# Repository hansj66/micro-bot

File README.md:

# Micro:bit sumo robot
Firmware and hardware design files for the [TimeExpander.com](https://www.timeexpander.com/) Micro:bit based robot

The bot features two motor bridges, 3 x time of flight sensors, 4 x reflective object sensors and a GPIO Expander. 

Toolchain for building the firmware is the mBed online compiler.

You can watch one of the demo state machines in action here: https://youtu.be/_6B225iNg58

# V3
There is an untested v3 in the Hardware folder. [See v3 Readme](https://github.com/rosmo-robot/micro-bot/tree/master/Hardware/V3#readme)

# V2

This is the latest tested version.

# v2 Bill of materials
* 1 x Main PCB (https://github.com/hansj66/micro-bot/blob/master/Hardware/minisumo_v2.brd)
* 4 x line sensor PCBs (https://github.com/hansj66/micro-bot/blob/master/Hardware/minisumo_sensor.brd)
* 2 x Wheels (AliExpress)
* 2 x N20 motors (AliExpress)
* 2 x N20 motor bracket assembly (AliExpress)
* 3 x VL53L0X time of flight sensors on a carrier PCB (AliExpress)
* 1 x TCA9539 IO expander (Digikey)
* 1 x TXB0106PWR Bi-directional level translator  (Digikey)
* 4 x QRE1113GR Reflective optical sensors  (Digikey)
* 1 x 100uF aluminium capacitor
* 1 x 2x5 pin 2.54mm female header (Digikey)
* 1 x battery pack for 4x AAA  (Digikey)
* 1 x JS202011SCQN slide switch  (Digikey)
* 1 x SOT223 LM1117 3.3V regulator (Digikey)
* 1 x Mini caster assembly (AliExpress + 3D printed bracket)
* 2 x 3D printed spacers (between motors and PCB)
* 1 x 12 pin male breakaway header  (Digikey)
* 3 x 6 pin RA breakaway header  (Digikey)
* 1 x hook and loop tape (for attaching battery pack)
* 2 x 100nf capacitors (motor noise suppression)

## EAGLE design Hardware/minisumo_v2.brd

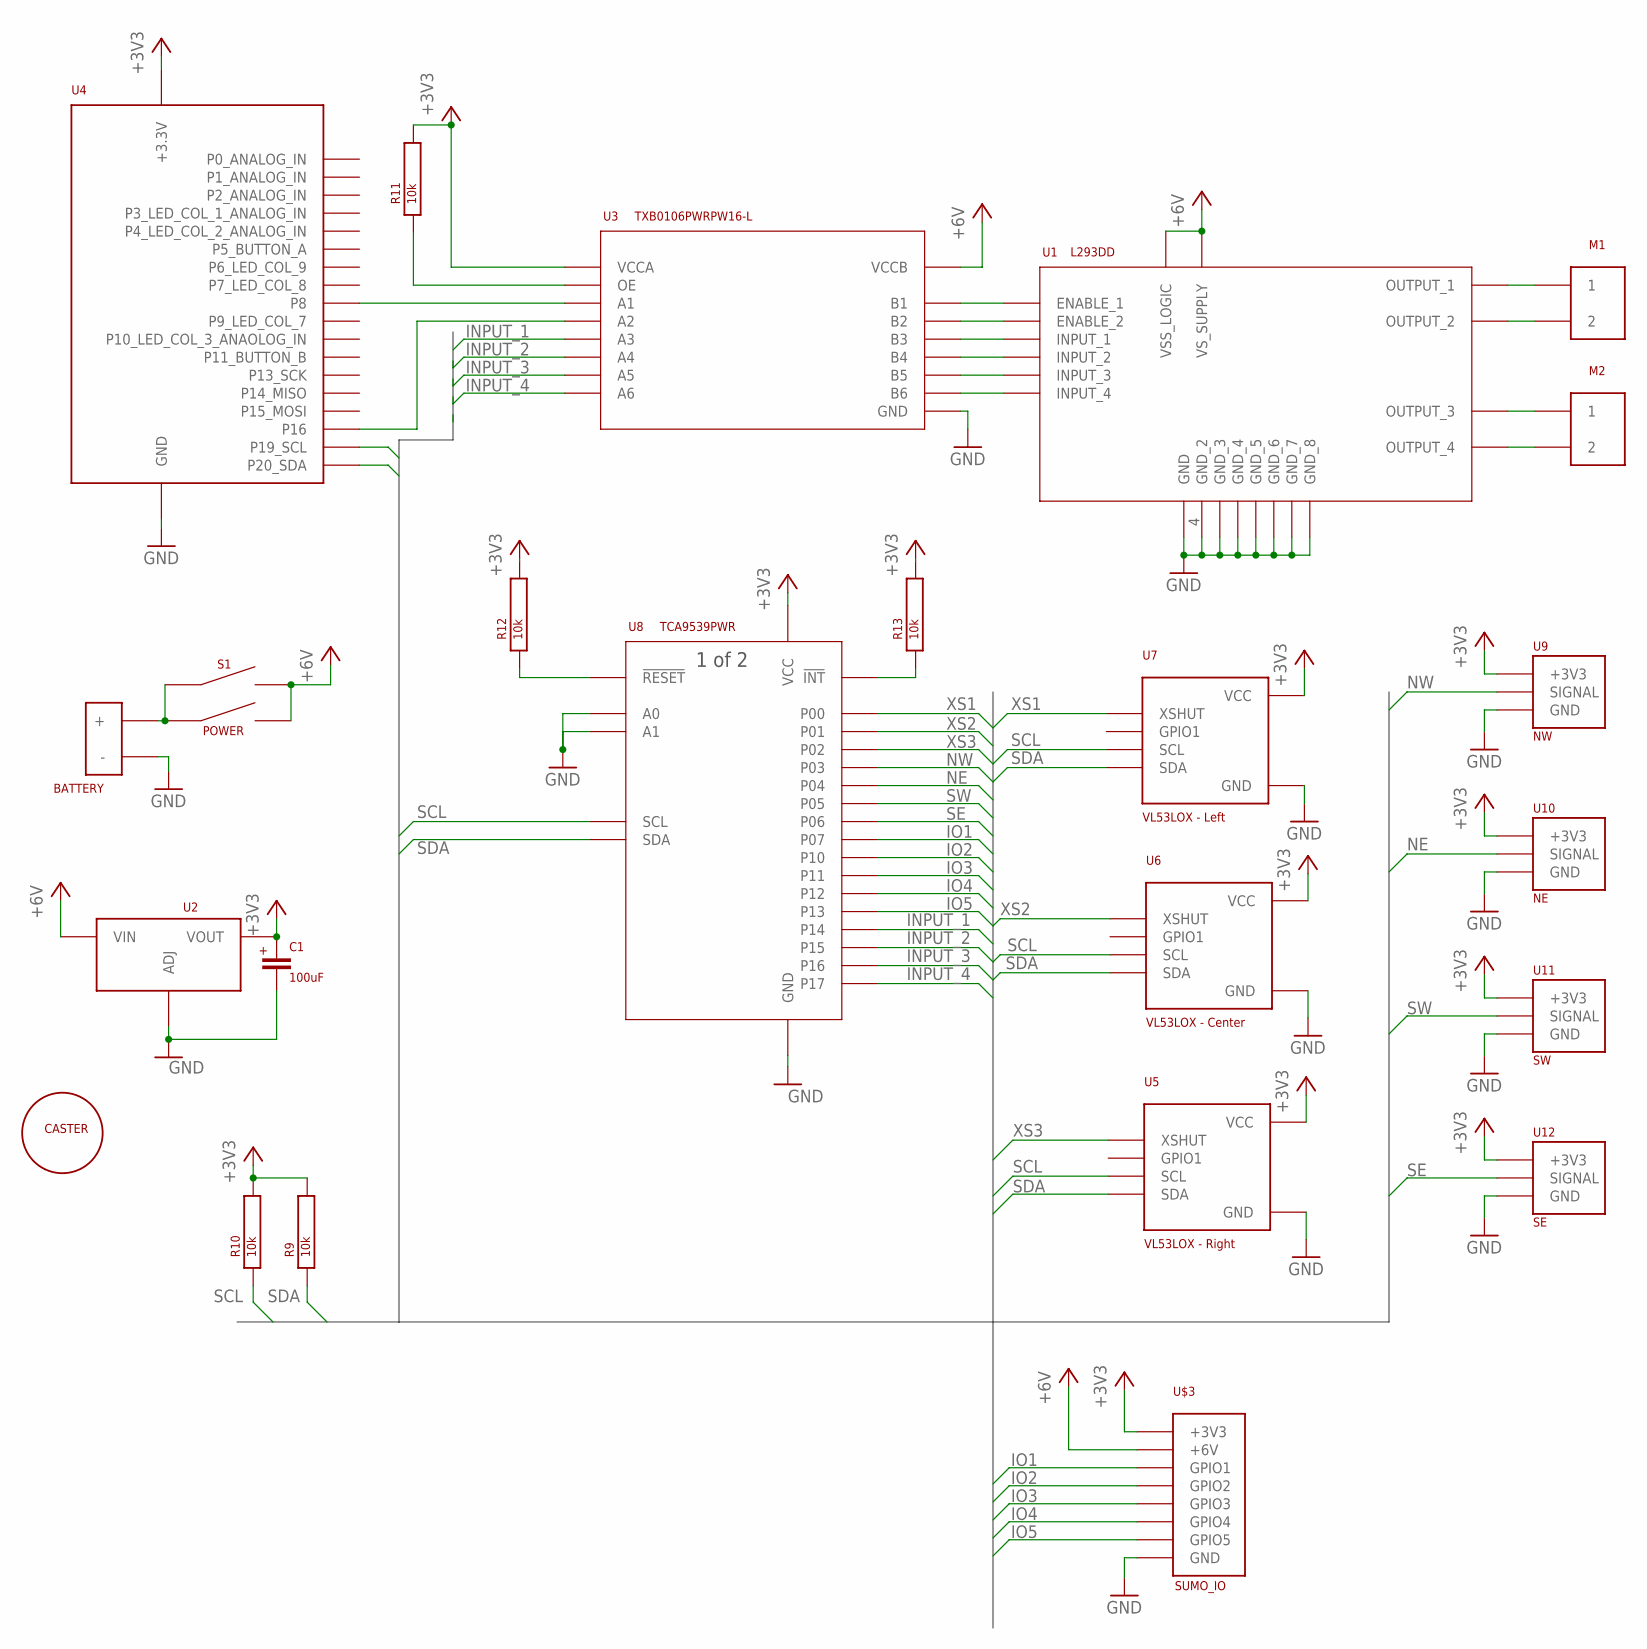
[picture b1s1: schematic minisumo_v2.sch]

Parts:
BATTERY: BATTERY_HOLDER_AAA_2X2
C1: 100uF; ALUMINUM_WURTH_100UF_865080243007
M1, M2: N20_MOTOR; N20-MOTOR-BRACKET
R9, R10, R11, R12, R13: 10k; RES_0402
S1: POWER; SWITCH_JS202011SCQN
U1: L293DD; SO-20
U2: LM1117; SOT-223
U3: TXB0106PWRPW16-L; PW16-L
U4: BBC Micro:bit; CYCLONE_MICROBIT_VERTICAL
U5: VL53LOX - Right; VL53LOX
U6: VL53LOX - Center; VL53LOX
U7: VL53LOX - Left; VL53LOX
U8: TCA9539PWR; 24-TSSOP
U9: NW; QRE1113_MODULE
U10: NE; QRE1113_MODULE
U11: SW; QRE1113_MODULE
U12: SE; QRE1113_MODULE
U$1: CASTER
U$3: SUMO_IO

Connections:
+3V3: C1.+, R9.P$2, R10.P$2, R11.P$2, R12.P$2, R13.P$2, U2.P$2 (VOUT), U2.VOUT$1 (VOUT), U3.2 (VCCA), U4.3.3V@9 (+3.3V), U4.3.3V@10 (+3.3V), U4.3.3V@11 (+3.3V), U4.3.3V@12 (+3.3V), U4.3.3V@13 (+3.3V), U4.3.3V@14 (+3.3V), U5.VCC, U6.VCC, U7.VCC, U8.24 (VCC), U9.+3V3, U10.+3V3, U11.+3V3, U12.+3V3, U$3.3V3 (+3V3)
+5V: S1.3 (B2), S1.6 (B1), U1.10 (VS_SUPPLY), U1.20 (VSS_LOGIC), U2.VIN, U3.15 (VCCB), U$3.6V (+6V)
GND: BATTERY.-, C1.-, U1.4 (GND_2), U1.5 (GND_3), U1.6 (GND_4), U1.7 (GND_5), U1.14 (GND_6), U1.15 (GND_7), U1.16 (GND_8), U1.17 (GND), U2.GND (ADJ), U3.9 (GND), U4.GND@1 (GND), U4.GND@2 (GND), U4.GND@3 (GND), U4.GND@4 (GND), U4.GND@5 (GND), U4.GND@6 (GND), U5.GND, U6.GND, U7.GND, U8.2 (A1), U8.12 (GND), U8.21 (A0), U9.GND, U10.GND, U11.GND, U12.GND, U$3.GND
INPUT_1: U3.4 (A3), U8.17 (P14)
INPUT_2: U3.5 (A4), U8.18 (P15)
INPUT_3: U3.6 (A5), U8.19 (P16)
INPUT_4: U3.7 (A6), U8.20 (P17)
IO1: U8.11 (P07), U$3.GPIO1
IO2: U8.13 (P10), U$3.GPIO2
IO3: U8.14 (P11), U$3.GPIO3
IO4: U8.15 (P12), U$3.GPIO4
IO5: U8.16 (P13), U$3.GPIO5
unnamed: U1.1 (ENABLE_1), U3.16 (B1)
unnamed: U1.11 (ENABLE_2), U3.14 (B2)
unnamed: U1.2 (INPUT_1), U3.13 (B3)
unnamed: U1.9 (INPUT_2), U3.12 (B4)
unnamed: M1.1, U1.3 (OUTPUT_1)
unnamed: M1.2, U1.8 (OUTPUT_2)
unnamed: M2.1, U1.13 (OUTPUT_3)
unnamed: M2.2, U1.18 (OUTPUT_4)
unnamed: U3.1 (A1), U4.P8
unnamed: U1.12 (INPUT_3), U3.11 (B5)
unnamed: U3.3 (A2), U4.P16
unnamed: U1.19 (INPUT_4), U3.10 (B6)
unnamed: BATTERY.+, S1.2 (A2), S1.5 (A1)
unnamed: R11.P$1, U3.8 (OE)
unnamed: R12.P$1, U8.3 (!RESET)
unnamed: R13.P$1, U8.1 (!INT)
NE: U8.8 (P04), U10.SIGNAL
NW: U8.7 (P03), U9.SIGNAL
SCL: R10.P$1, U4.P21_SCL (P19_SCL), U5.SCL, U6.SCL, U7.SCL, U8.22 (SCL)
SDA: R9.P$1, U4.P20_SDA, U5.SDA, U6.SDA, U7.SDA, U8.23 (SDA)
SE: U8.10 (P06), U12.SIGNAL
SW: U8.9 (P05), U11.SIGNAL
XS1: U7.XSHUT, U8.4 (P00)
XS2: U6.XSHUT, U8.5 (P01)
XS3: U5.XSHUT, U8.6 (P02)

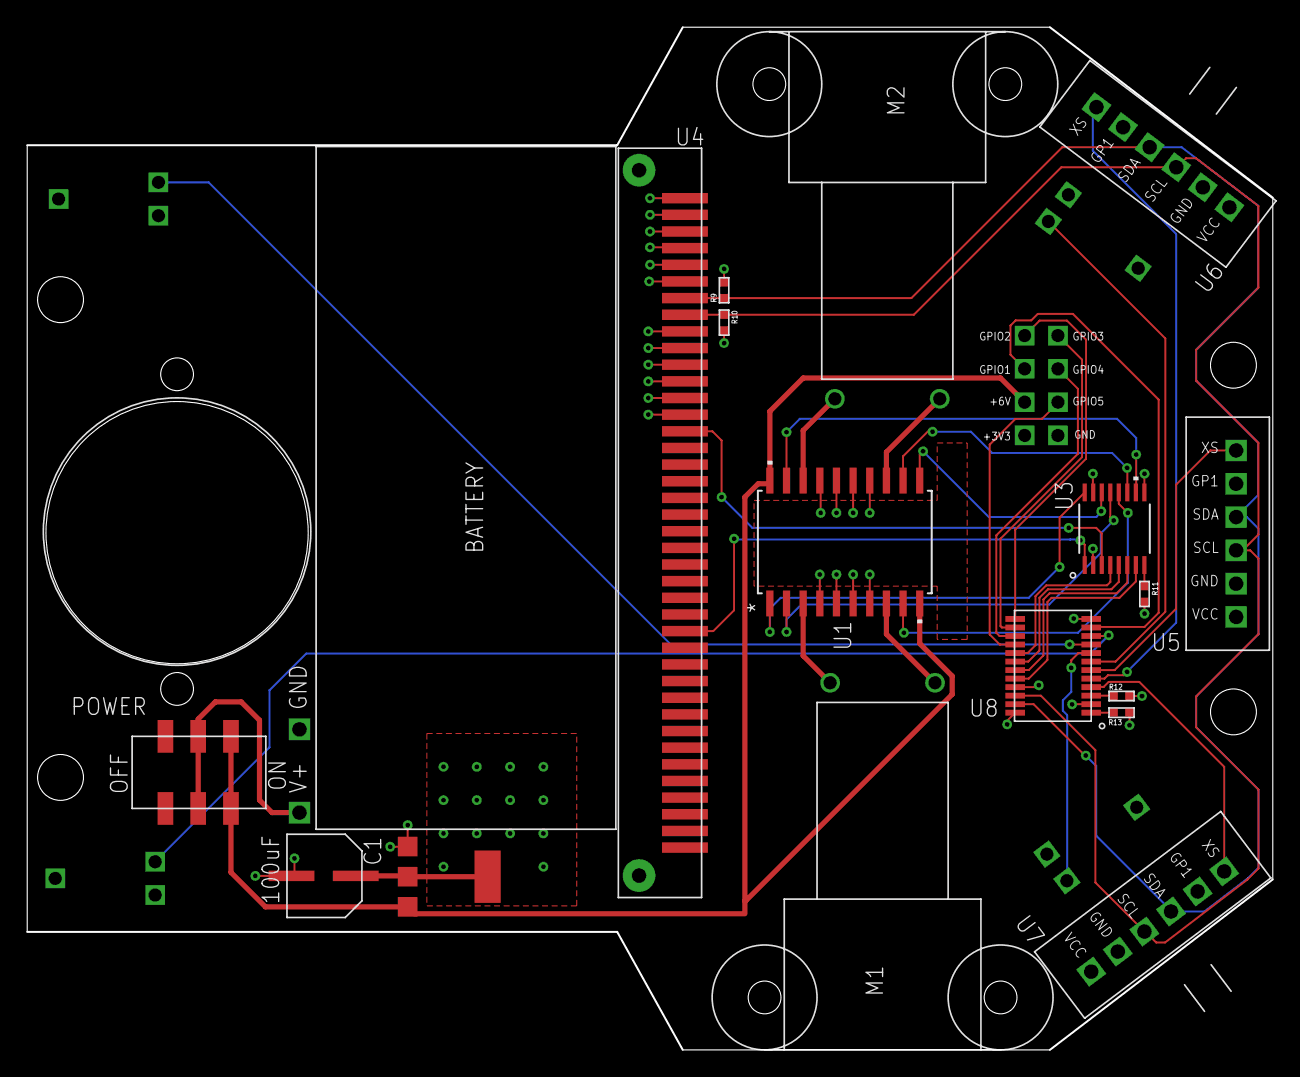
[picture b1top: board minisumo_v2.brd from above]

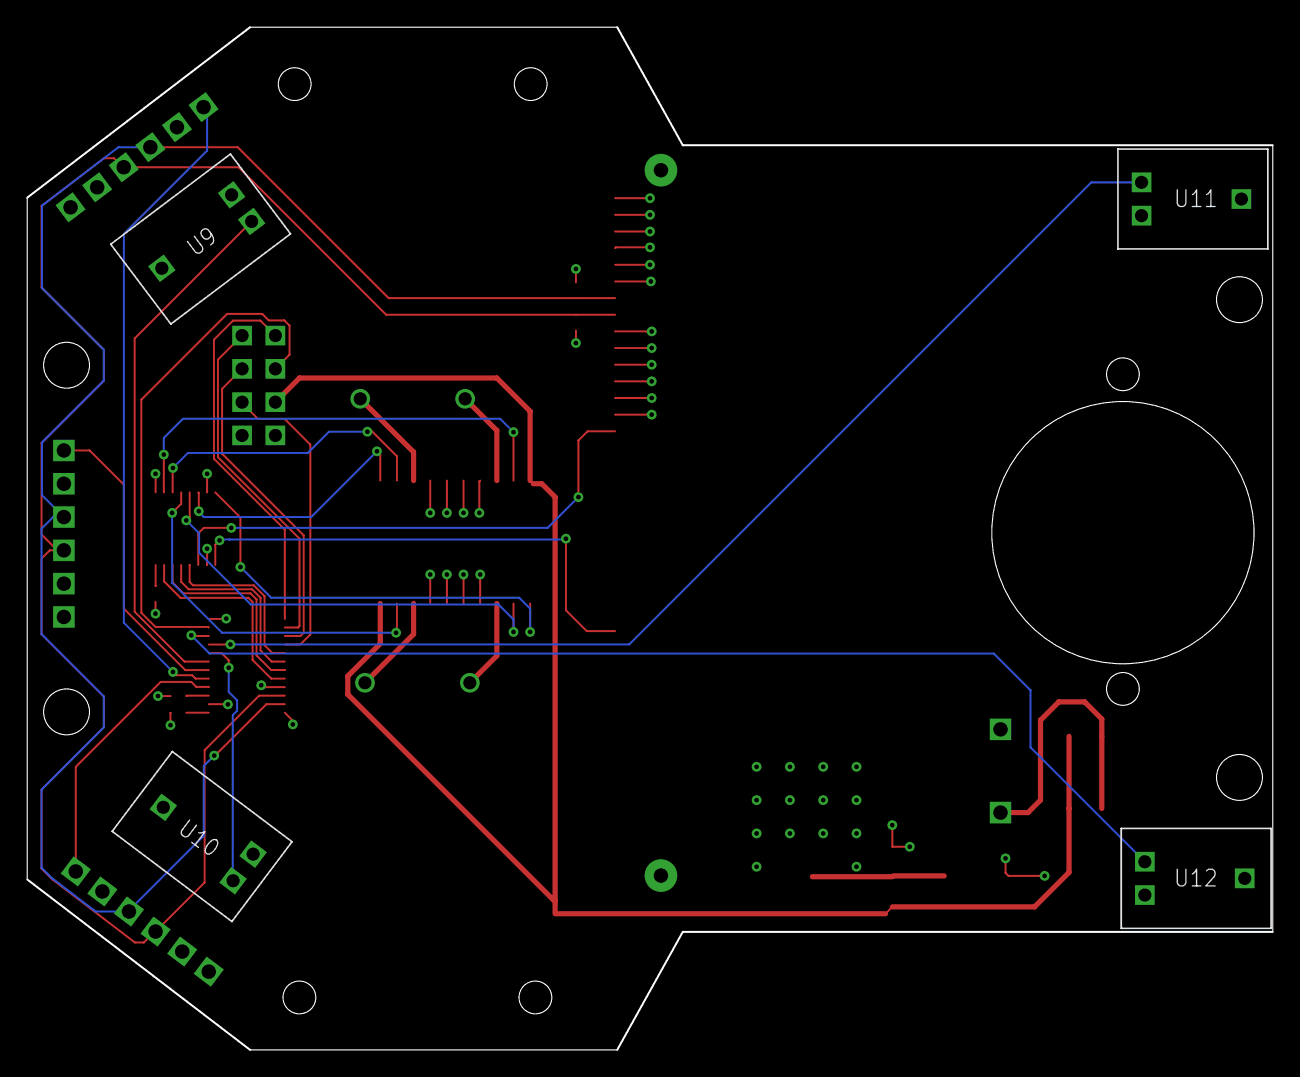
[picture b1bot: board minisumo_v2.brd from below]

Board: 4 copper layers, 95.0 x 78.0 mm, 24 parts (4 on the bottom side), 37 nets.

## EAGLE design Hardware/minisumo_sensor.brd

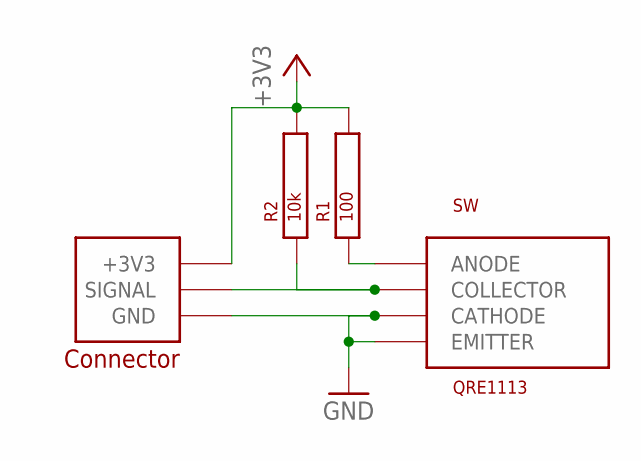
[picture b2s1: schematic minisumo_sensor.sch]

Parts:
R1: 100; RES_0402
R2: 10k; RES_0402
SW: QRE1113
U$1: QRE1113_CONNECTOR

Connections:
+3V3: R1.P$2, R2.P$2, U$1.+3V3
GND: SW.CATHODE, SW.EMITTER, U$1.GND
unnamed: R2.P$1, SW.COLLECTOR, U$1.SIGNAL
unnamed: R1.P$1, SW.ANODE

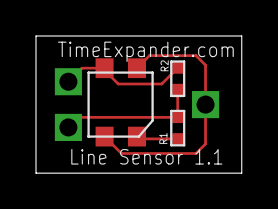
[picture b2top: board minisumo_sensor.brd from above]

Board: 2 copper layers, 11.4 x 7.6 mm, 4 parts (0 on the bottom side), 4 nets.

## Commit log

2020-01-03 Verified VL53L0X, QRE1113, L293DD and TXB0106
2020-01-12 Feature complete * using arduino framework
2020-02-12 Ported from arduino framework to mbed framework * Added harware selftest option on boot * Minor tweaks in Polulu VL53L0X library * Added a few visuals for the test sequence
2020-02-13 Added motor test
2020-02-13 Added range test visualization
2020-02-29 Added hardware design files. * Moved the firmware to online mbed * Added two demo state machines
2020-02-29 Added license information
2020-02-29 Removed comment regarding fixed issue
2022-09-08 kicad 6 project
2022-09-08 Zip of Kicad 6 project
2022-09-08 Added link to 2.1 documentation
2022-09-09 Zip of Kicad6 project
2022-09-09 Fix switch footprint
2022-09-10 Schematic
2022-09-18 Adds rosmo pinout
    Uses common IR sensors, uses lipo battery shield
